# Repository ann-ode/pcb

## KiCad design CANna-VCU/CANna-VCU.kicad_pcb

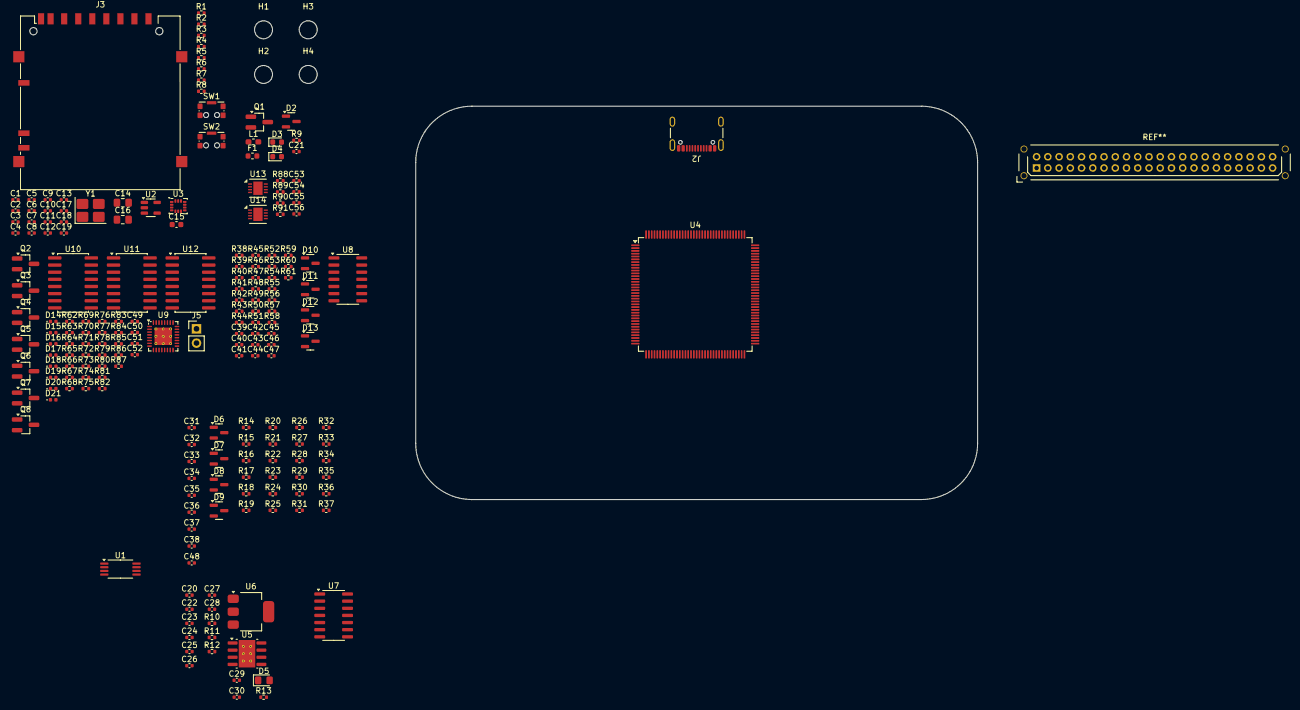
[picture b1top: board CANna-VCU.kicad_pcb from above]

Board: 2 copper layers, 201 parts (0 on the bottom side), 110 nets, no tracks yet.

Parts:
C1, C24, C50, C51: 0.1uF; C_0402_1005Metric
C2, C20, C21: 10uF; C_0402_1005Metric
C3: 68nF; C_0402_1005Metric
C4, C9, C11, C12, C13, C17, C18: 100nF; C_0402_1005Metric
C5, C6, C29, C31, C32, C33, C34, C39, C40, C41, C42, C47, C48, C53, C54: 100n; C_0402_1005Metric
C7, C8: 4.7pF; C_0402_1005Metric
C10: 4.7uF; C_0402_1005Metric
C14, C16: 2.2u; C_0805_2012Metric_Pad1.18x1.45mm_HandSolder
C15: 100nF; C_0603_1608Metric
C19, C23, C49, C52: 1uF; C_0402_1005Metric
C22: 220nF; C_0402_1005Metric
C25, C26, C27, C28: 22uF; C_0402_1005Metric
C30: 10u; C_0402_1005Metric
C35, C36, C37, C38, C43, C44, C45, C46: 1n; C_0402_1005Metric
C55, C56: 4.7n; C_0402_1005Metric
D2: BZX84Cxx; SOT-23
D3, D4: D_Schottky; D_0603_1608Metric
D5: LED; LED_0805_2012Metric_Pad1.15x1.40mm_HandSolder
D6, D7, D8, D9, D10, D11, D12, D13: BZX84-C3V3; SOT-23
D14, D15, D16, D17, D18, D19, D20, D21: LED; LED_0402_1005Metric
F1: 500mA; Fuse_0603_1608Metric
H1, H2, H3, H4: M3; MountingHole_3.2mm_M3
J2: USB_C_Receptacle_USB2.0_16P; USB_C_Receptacle_GCT_USB4105-xx-A_16P_TopMnt_Horizontal
J3: SD_Card_Device; SD_Hirose_DM1AA_SF_PEJ82
J5: FSUK_RTD; PinHeader_1x02_P2.54mm_Vertical
L1: L; L_0603_1608Metric_Pad1.05x0.95mm_HandSolder
Q1, Q2, Q3, Q4, Q5, Q6, Q7, Q8: FDN359BN; SOT-23_Handsoldering
R1, R2: 5.1k; R_0402_1005Metric
R3: 100K; R_0402_1005Metric
R4: 1.3K; R_0402_1005Metric
R5, R6: 10K; R_0402_1005Metric
R7, R8: 2.2K; R_0402_1005Metric
R9, R10, R11, R14, R15, R16, R17, R38, R39, R40, R41: 100k; R_0402_1005Metric
R12: 22k; R_0402_1005Metric
R13: 1k5; R_0402_1005Metric
R18, R19, R20, R21, R42, R43, R44, R45, R76: 1k; R_0402_1005Metric
R22, R26, R30, R34, R46, R50, R54, R58: 75k; R_0402_1005Metric
R23, R24, R27, R28, R31, R32, R35, R36, R47, R48, R51, R52, R55, R56, R59, R60: 5.6k; R_0402_1005Metric
R25, R29, R33, R37, R49, R53, R57, R61: 1.8k; R_0402_1005Metric
R62, R63, R64, R65, R66, R67, R68, R69: 1.5K; R_0402_1005Metric
R70, R71, R72: 8.6K; R_0402_1005Metric
R73, R74, R81, R82, R83, R84: 0; R_0402_1005Metric
R75: 4.7K; R_0402_1005Metric
R77: 3k3; R_0402_1005Metric
R78, R79, R80, R85, R86, R87: 1K; R_0402_1005Metric
R88, R89, R90, R91: 60R; R_0402_1005Metric
SW1, SW2: CK_KMS2xxG; SW_SPST_CK_KMS2xxGP
U1: M24256-DRD; TSSOP-8_4.4x3mm_P0.65mm
U2: MCP9800Ax-xOT; SOT-23-5
U3: ISM330DHCX; LGA-14_3x2.5mm_P0.5mm_LayoutBorder3x4y
U4: STM32F746ZGT6; LQFP-144_20x20mm_P0.5mm
U5: LMR33630CDDA; Texas_R-PDSO-G8_EP2.95x4.9mm_Mask2.4x3.1mm_ThermalVias
U6: LD1117S33TR_SOT223; SOT-223-3_TabPin2
U7, U8: TLV274; SOIC-14_3.9x8.7mm_P1.27mm
U9: TQFN-32-1EP_5x5mm_P0.5mm_EP3.1x3.1mm_ThermalVias
U10, U11, U12: 4504; SOIC-16W_5.3x10.2mm_P1.27mm
U13, U14: LTC2875-DD; DFN-8-1EP_3x3mm_P0.5mm_EP1.66x2.38mm
Y1: 25MHz; Crystal_SMD_3225-4Pin_3.2x2.5mm_HandSoldering

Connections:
0_CANH: R88.2, U13.7 (CANH)
0_CANL: R89.1, U13.6 (CANL)
1_CANH: R90.2, U14.7 (CANH)
1_CANL: R91.1, U14.6 (CANL)
+3V3: C1.2, C2.2, C4.2, C5.2, C6.2, C9.1, C10.1, C11.1, C12.1, C13.1, C15.1, C17.1, C51.2, C52.2, C53.2, C54.2, J3.4 (VDD), R3.2, R5.2, R6.2, R7.2, R8.2, SW1.1, SW2.1, U1.1 (E0), U1.2 (E1), U1.3 (E2), U1.8 (VCC), U2.1 (V_{DD}), U3.5 (VDDIO), U3.8 (VDD), U4.6 (VBAT), U4.17 (VDD), U4.30 (VDD), U4.39 (VDD), U4.52 (VDD), U4.62 (VDD), U4.72 (VDD), U4.84 (VDD), U4.95 (VDDUSB), U4.108 (VDD), U4.121 (VDD), U4.131 (VDD), U4.144 (VDD), U9.28 (RDYEN), U9.31 (VDD3), U10.16 (VDD), U11.1 (VCC), U12.1 (VCC), U13.3 (VCC), U14.3 (VCC)
+3V3A: C18.1, C19.1, U4.33 (VDDA)
+5V: R74.2, R81.2, R82.2
+5V_UNPROT: F1.1, J2.A4 (VBUS), J2.A9 (VBUS), J2.B4 (VBUS), J2.B9 (VBUS)
+12V: C47.2, C48.2, U7.4 (V+), U8.4 (V+)
+GLV_PROT: C20.1, C21.1, C22.1, C49.2, C50.2, D2.3 (K), Q1.2 (S), R70.1, R73.2, R83.2, R84.2, U5.2 (VIN), U5.3 (EN), U9.30 (VDD24)
/ADC/APPS_1_IN: R17.1, R21.1, R41.1, R45.1
/ADC/APPS_1_OUT: C36.2, C44.2, D9.3 (K), D13.3 (K), R35.2, R36.1, R59.2, R60.1
/ADC/APPS_2_IN: R16.1, R20.1, R40.1, R44.1
/ADC/APPS_2_OUT: C35.2, C43.2, D8.3 (K), D12.3 (K), R31.2, R32.1, R55.2, R56.1
/ADC/BPS_IN: R14.1, R18.1, R38.1, R42.1
/ADC/BPS_OUT: C37.2, C45.2, D6.3 (K), D10.3 (K), R23.2, R24.1, R47.2, R48.1
/ADC/SAGL_IN: R15.1, R19.1, R39.1, R43.1
/ADC/SAGL_OUT: C38.2, C46.2, D7.3 (K), D11.3 (K), R27.2, R28.1, R51.2, R52.1
/HSIO/LEVEL1_RDY: R75.2, U9.29 (READY)
/HSIO/LSDI_GP3: U9.15 (OP7), U9.16 (OP8)
/HSIO/LSD_R2D: Q2.1 (G), R77.2
/HSIO/R2DS-: J5.2, R76.2
/MCU/I2C_CLK: U2.4 (SCLK), U3.13 (SCL)
/MCU/I2C_SCL: R8.1, U1.6 (SCL), U4.139 (PB8)
/MCU/I2C_SDA: R7.1, U1.5 (SDA), U2.5 (SDA), U3.14 (SDA), U4.140 (PB9)
/MCU/OSC_IN: C8.1, U4.23 (PH0), Y1.1
/MCU/OSC_OUT: R4.1, U4.24 (PH1)
/MCU/RST: R5.1, U4.25 (NRST)
/MCU/USB_D+: J2.A6 (D+), J2.B6 (D+), U4.104 (PA12)
/MCU/USB_D-: J2.A7 (D-), J2.B7 (D-), U4.103 (PA11)
/MCU/nRST: C3.2, R3.1, U4.134 (PB4)
/Power/+3.3V: C30.1, D5.2 (A), U6.2 (VO)
/Power/BOOT0: C24.1, U5.7 (BOOT)
/Power/FB1: R11.1, R12.2, U5.5 (FB)
/Power/PG1: R10.1, U5.4 (PG)
/Power/PWR_LED_K: D5.1 (K), R13.1
/Power/SW1: C24.2, L1.1, U5.8 (SW)
/Power/VCC1: C23.1, R10.2, U5.6 (VCC)
GND: C1.1, C2.1, C3.1, C4.1, C5.1, C6.1, C7.2, C8.2, C9.2, C10.2, C11.2, C12.2, C13.2, C14.1, C15.2, C16.1, C17.2, C18.2, C19.2, C20.2, C21.2, C22.2, C23.2, C25.2, C26.2, C27.2, C28.2, C29.2, C30.2, C31.1, C32.1, C33.1, C34.1, C35.1, C36.1, C37.1, C38.1, C39.1, C40.1, C41.1, C42.1, C43.1, C44.1, C45.1, C46.1, C47.1, C48.1, C49.1, C50.1, C51.1, C52.1, C53.1, C54.1, C55.2, C56.2, D6.1 (A), D7.1 (A), D8.1 (A), D9.1 (A), D10.1 (A), D11.1 (A), D12.1 (A), D13.1 (A), D14.1 (K), D15.1 (K), D16.1 (K), D17.1 (K), D18.1 (K), D19.1 (K), D20.1 (K), D21.1 (K), J2.A1 (GND), J2.A12 (GND), J2.B1 (GND), J2.B12 (GND), J2.S1 (SHIELD), J3.3 (VSS), J3.6 (VSS), Q2.2 (S), Q3.2 (S), Q4.2 (S), Q5.2 (S), Q6.2 (S), Q7.2 (S), Q8.2 (S), R1.1, R2.1, R9.1, R12.1, R13.2, R14.2, R15.2, R16.2, R17.2, R25.2, R29.2, R33.2, R37.2, R38.2, R39.2, R40.2, R41.2, R49.2, R53.2, R57.2, R61.2, R71.2, R72.2, R75.1, R77.1, SW1.2, SW1.SH (B), SW2.2, SW2.SH (B), U1.4 (VSS), U2.2 (GND), U3.2 (SDx), U3.3 (SCx), U3.6 (GND), U3.7 (GND), U4.16 (VSS), U4.31 (VSSA), U4.38 (VSS), U4.51 (VSS), U4.61 (VSS), U4.83 (VSS), U4.94 (VSS), U4.107 (VSS), U4.120 (VSS), U4.130 (VSS), U5.1 (PGND), U6.1 (GND), U7.11 (V-), U8.11 (V-), U9.25 (GND), U9.32 (GND), U10.8 (VSS), U11.8 (VSS), U12.8 (VSS), U13.2 (GND), U13.8 (RS), U13.9 (GND), U14.2 (GND), U14.8 (RS), U14.9 (GND), Y1.2, Y1.4
unnamed: C7.1, R4.2, Y1.3
unnamed: D2.1 (A), Q1.1 (G), R9.2
unnamed: D3.2 (A), F1.2
unnamed: C29.1, D3.1 (K), D4.1 (K), U6.3 (VI)
unnamed: C25.1, C26.1, C27.1, C28.1, D4.2 (A), L1.2, R11.2
unnamed: D14.2 (A), U9.2 (LED1)
unnamed: D15.2 (A), U9.4 (LED2)
unnamed: D16.2 (A), U9.6 (LED3)
unnamed: D17.2 (A), U9.8 (LED4)
unnamed: D18.2 (A), U9.17 (LED5)
unnamed: D19.2 (A), U9.19 (LED6)
unnamed: D20.2 (A), U9.21 (LED7)
unnamed: D21.2 (A), U9.23 (LED8)
unnamed: J2.A5 (CC1), R1.2
unnamed: J2.B5 (CC2), R2.2
unnamed: J5.1, Q2.3 (D), R76.1
unnamed: Q3.3 (D), R78.1
unnamed: Q4.3 (D), R79.1
unnamed: Q5.3 (D), R80.1
unnamed: Q6.3 (D), R85.1
unnamed: Q7.3 (D), R86.1
unnamed: Q8.3 (D), R87.1
unnamed: R22.2, R23.1
unnamed: R24.2, R25.1
unnamed: R26.2, R27.1
unnamed: R28.2, R29.1
unnamed: R30.2, R31.1
unnamed: R32.2, R33.1
unnamed: R34.2, R35.1
unnamed: R36.2, R37.1
unnamed: R46.2, R47.1
unnamed: R48.2, R49.1
unnamed: R50.2, R51.1
unnamed: R52.2, R53.1
unnamed: R54.2, R55.1
unnamed: R56.2, R57.1
unnamed: R58.2, R59.1
unnamed: R60.2, R61.1
unnamed: C14.2, U4.71 (VCAP_1)
unnamed: C16.2, U4.106 (VCAP_2)
unnamed: C32.2, R19.2, U7.3 (+)
unnamed: R26.1, U7.1, U7.2 (-)
unnamed: C31.2, R18.2, U7.5 (+)
unnamed: R22.1, U7.6 (-), U7.7
unnamed: C34.2, R21.2, U7.10 (+)
unnamed: R34.1, U7.8, U7.9 (-)
unnamed: C33.2, R20.2, U7.12 (+)
unnamed: R30.1, U7.13 (-), U7.14
unnamed: C40.2, R43.2, U8.3 (+)
unnamed: R50.1, U8.1, U8.2 (-)
unnamed: C39.2, R42.2, U8.5 (+)
unnamed: R46.1, U8.6 (-), U8.7
unnamed: C42.2, R45.2, U8.10 (+)
unnamed: R58.1, U8.8, U8.9 (-)
unnamed: C41.2, R44.2, U8.12 (+)
unnamed: R54.1, U8.13 (-), U8.14
unnamed: R70.2, R71.1, U9.27 (EXTVM)
unnamed: R62.1, U9.1 (IN1)
unnamed: R63.1, U9.3 (IN2)
unnamed: R64.1, U9.5 (IN3)
unnamed: R65.1, U9.7 (IN4)
unnamed: R66.1, U9.18 (IN5)
unnamed: R67.1, U9.20 (IN6)
unnamed: R68.1, U9.22 (IN7)
unnamed: R69.1, U9.24 (IN8)
unnamed: R72.1, U9.26 (REFDI)
unnamed: R73.1, R74.1, U10.1 (VCC)
unnamed: R81.1, R83.1, U11.16 (VDD)
unnamed: R82.1, R84.1, U12.16 (VDD)
unnamed: C55.1, R88.1, R89.2, U13.5 (SPLIT)
unnamed: C56.1, R90.1, R91.2, U14.5 (SPLIT)

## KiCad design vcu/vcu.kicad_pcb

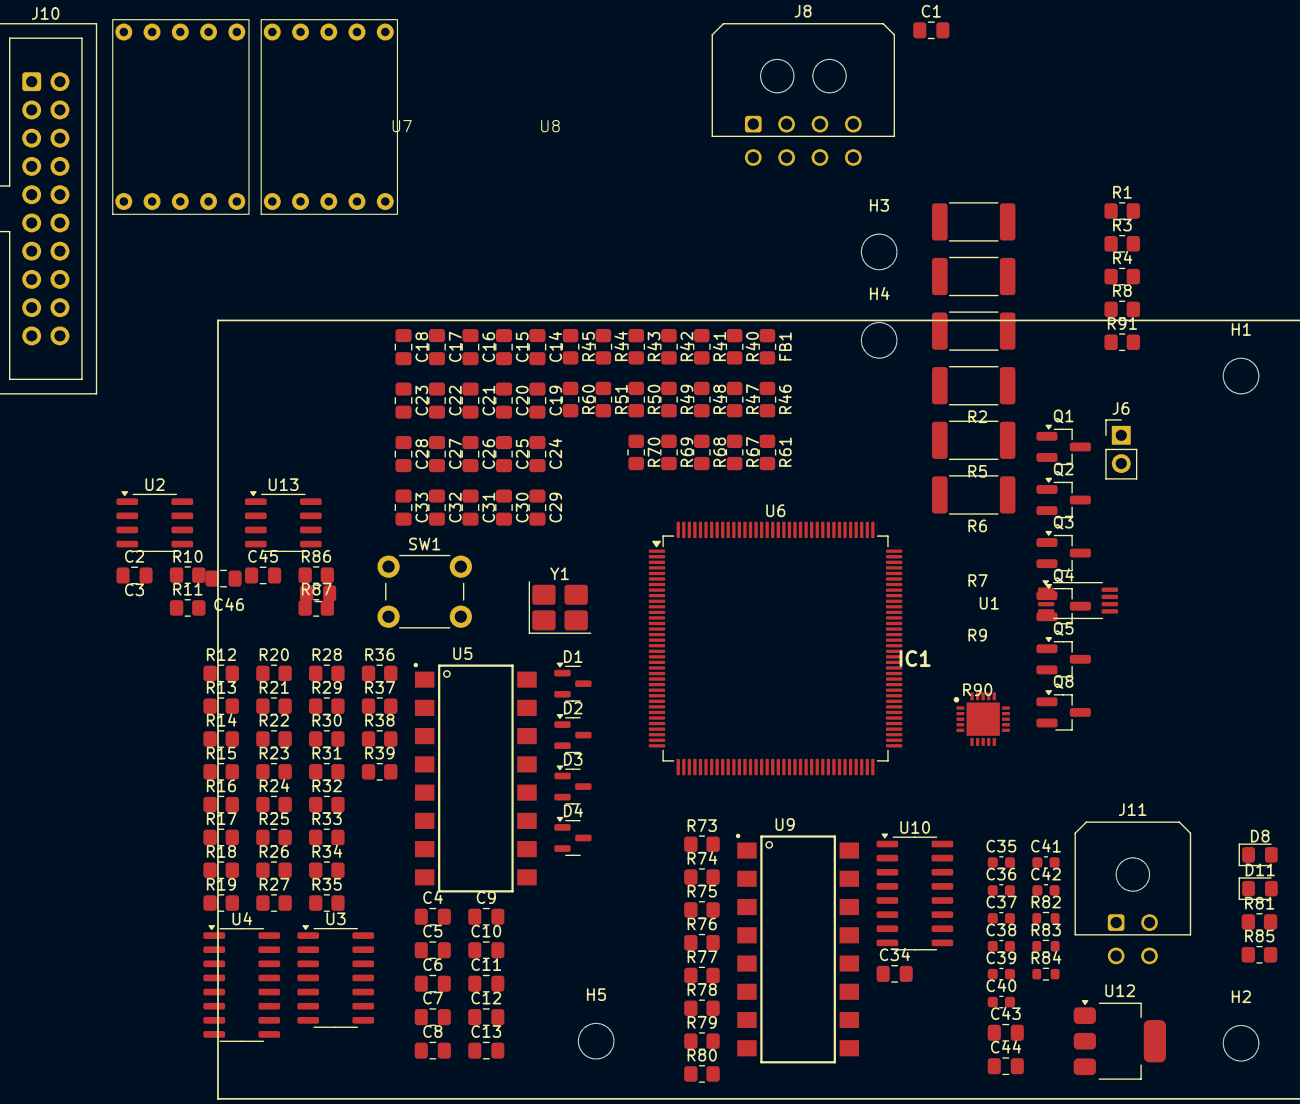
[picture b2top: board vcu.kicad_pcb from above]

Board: 4 copper layers, 157 parts (0 on the bottom side), 123 nets, no tracks yet.

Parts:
C1, C2, C4, C5, C6, C7, C12, C13, C15, C19, C20, C21, C22, C23, C24, C25, C26, C27, C28, C29, C30, C33, C34, C43, C45: 100n; C_0805_2012Metric_Pad1.18x1.45mm_HandSolder
C3, C46: 4.7n; C_0805_2012Metric_Pad1.18x1.45mm_HandSolder
C8, C9, C10, C11: 1n; C_0805_2012Metric_Pad1.18x1.45mm_HandSolder
C14, C16: 4.3p; C_0805_2012Metric_Pad1.18x1.45mm_HandSolder
C17, C18: 2.2u; C_0805_2012Metric_Pad1.18x1.45mm_HandSolder
C31: 4.7u; C_0805_2012Metric_Pad1.18x1.45mm_HandSolder
C32: 1u; C_0805_2012Metric_Pad1.18x1.45mm_HandSolder
C35: 10uF; C_0603_1608Metric
C36: 220nF; C_0603_1608Metric
C37: 1uF; C_0603_1608Metric
C38: 0.1uF; C_0603_1608Metric
C39, C40, C41, C42: 22uF; C_0603_1608Metric
C44: 10u; C_0805_2012Metric_Pad1.18x1.45mm_HandSolder
D1, D2, D3, D4: BZX84-C3V3; SOT-23
D8, D11: LED; LED_0805_2012Metric_Pad1.15x1.40mm_HandSolder
FB1: 120; R_0805_2012Metric_Pad1.20x1.40mm_HandSolder
H1, H2, H3, H4, H5: M3; MountingHole_3.2mm_M3
IC1: MAX20040DATPA_VY+; QFN50P400X400X80-21N-D
J6: FSUK_RTD; PinHeader_1x02_P2.54mm_Vertical
J8: OUT; Molex_Micro-Fit_3.0_43045-0800_2x04_P3.00mm_Horizontal
J10: Conn_ARM_JTAG_SWD_20; IDC-Header_2x10_P2.54mm_Vertical
J11: PWR; Molex_Micro-Fit_3.0_43045-0400_2x02_P3.00mm_Horizontal
Q1, Q2, Q3, Q4, Q5, Q8: FDN359BN; SOT-23_Handsoldering
R1, R3, R4, R40, R60, R61, R67, R68, R69, R70, R77, R78, R79, R80, R91: 10k; R_0805_2012Metric_Pad1.20x1.40mm_HandSolder
R2, R5, R6, R7, R9, R90: 1k; R_2512_6332Metric_Pad1.40x3.35mm_HandSolder
R8: 3k3; R_0805_2012Metric_Pad1.20x1.40mm_HandSolder
R10, R11, R86, R87: 60R; R_0805_2012Metric_Pad1.20x1.40mm_HandSolder
R12, R13, R14, R15: 100k; R_0805_2012Metric_Pad1.20x1.40mm_HandSolder
R16, R17, R18, R19, R36, R37, R38, R39: 1k; R_0805_2012Metric_Pad1.20x1.40mm_HandSolder
R20, R24, R28, R32: 75k; R_0805_2012Metric_Pad1.20x1.40mm_HandSolder
R21, R22, R25, R26, R29, R30, R33, R34: 5.6k; R_0805_2012Metric_Pad1.20x1.40mm_HandSolder
R23, R27, R31, R35: 1.8k; R_0805_2012Metric_Pad1.20x1.40mm_HandSolder
R41, R42, R43, R44, R45, R46, R47, R48, R49, R50, R51: 100; R_0805_2012Metric_Pad1.20x1.40mm_HandSolder
R73, R74, R75, R76: 220; R_0805_2012Metric_Pad1.20x1.40mm_HandSolder
R81: 3.3k; R_0805_2012Metric_Pad1.20x1.40mm_HandSolder
R82, R83: 100k; R_0603_1608Metric
R84: 22k; R_0603_1608Metric
R85: 1k5; R_0805_2012Metric_Pad1.20x1.40mm_HandSolder
SW1: SW_Push; SW_PUSH_6mm
U1: M24256-DRD; TSSOP-8_4.4x3mm_P0.65mm
U2, U13: MAX3051ESA+; SOIC-8_3.9x4.9mm_P1.27mm
U3: TLV274; SOIC-14_3.9x8.7mm_P1.27mm
U4, U10: HCF4010; SOIC-16_3.9x9.9mm_P1.27mm
U5, U9: ILQ615-4X009T; SOIC254P1005X380-16N
U6: STM32F746ZGT6; LQFP-144_20x20mm_P0.5mm
U7, U8: Vishay TDSG5160-MN 7-Segment Display
U12: LD1117S33TR_SOT223; SOT-223-3_TabPin2
Y1: 8MHz; Crystal_SMD_3225-4Pin_3.2x2.5mm_HandSoldering

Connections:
+3.3V: C1.1, C2.2, C19.1, C20.1, C21.1, C22.1, C23.1, C24.1, C25.1, C26.1, C27.1, C28.1, C29.1, C30.1, C31.1, C32.1, C44.1, C45.2, D11.2 (A), FB1.2, J10.1 (VTREF), J10.2 (VCC/NC), R60.2, R61.1, R67.2, R69.2, R70.2, U1.1 (E0), U1.2 (E1), U1.3 (E2), U1.8 (VCC), U2.3 (VDD), U5.10, U5.12, U5.14, U5.16, U6.6 (VBAT), U6.17 (VDD), U6.30 (VDD), U6.39 (VDD), U6.52 (VDD), U6.62 (VDD), U6.72 (VDD), U6.84 (VDD), U6.95 (VDDUSB), U6.108 (VDD), U6.121 (VDD), U6.131 (VDD), U6.144 (VDD), U12.2 (VO), U13.3 (VDD)
+3.3VA: C33.1, FB1.1, U6.32 (VREF+), U6.33 (VDDA)
+12V: C12.2, C13.2, C34.2, C35.1, C36.1, D8.2 (A), IC1.13 (IN), J8.5, U3.4 (V+), U4.1 (VCC), U4.16 (VDD), U9.10, U9.12, U9.14, U9.16, U10.1 (VCC), U10.16 (VDD)
+12VA: IC1.15 (OUT), IC1.16 (OUT_S)
/APPS_1_IN: R15.1, R19.1
/APPS_2_IN: R14.1, R18.1
/BMS_LATCHING_IN: Q2.3 (D), R5.2
/BPS_IN: R12.1, R16.1
/BRAKE_PRESSED: J8.2, U10.4 (Bout)
/CAN_C_H: R86.2, U13.7 (CANH)
/CAN_C_L: R87.1, U13.6 (CANL)
/CAN_S_H: R10.2, U2.7 (CANH)
/CAN_S_L: R11.1, U2.6 (CANL)
/DRS_BTN: R91.1, U4.9 (Din)
/DRS_PWM: J8.6, U10.10 (Dout)
/EEPROM_SCL: R61.2, U1.6 (SCL), U6.139 (PB8)
/EEPROM_SDA: R60.1, U1.5 (SDA), U6.140 (PB9)
/EEPROM_WC: U1.7 (WC), U6.96 (PC6)
/IMD_LATCHING_IN: Q1.3 (D), R2.2
/Input Shift/APPS_1_OUT: C9.2, D4.3 (K), R33.2, R34.1, U6.37 (PA3)
/Input Shift/APPS_2_OUT: C8.2, D3.3 (K), R29.2, R30.1, U6.29 (PC3)
/Input Shift/BPS_OUT: C10.2, D1.3 (K), R21.2, R22.1, U6.26 (PC0)
/Input Shift/DOUT_1: U5.15, U6.11 (PF1)
/Input Shift/DOUT_2: U5.13, U6.12 (PF2)
/Input Shift/DOUT_3: U5.11, U6.15 (PF5)
/Input Shift/DOUT_4: U5.9, U6.22 (PF10)
/Input Shift/SAGL_OUT: C11.2, D2.3 (K), R25.2, R26.1, U6.13 (PF3)
/Output Level Shifting/DIN_1: R73.1, U6.60 (PE9)
/Output Level Shifting/DIN_2: R74.1, U6.64 (PE11)
/Output Level Shifting/DIN_3: R75.1, U6.54 (PF14)
/Output Level Shifting/DIN_4: R76.1, U6.34 (PA0)
/Power/FB1: R83.1, R84.2
/Power/PWR_LED_K: D11.1 (K), R85.1
/Power/VCC1: C37.1, R82.2
/R2D_BTN: R3.1, U4.5 (Bin)
/R2D_SIREN_ON: Q5.1 (G), R8.2, U6.55 (PF15)
/RTDS-: J6.2, R9.2
/SAGL_IN: R13.1, R17.1
/SHDN_STATE: R1.1, U4.3 (Ain)
/STATUS: J8.1, U10.2 (Aout)
/STM32-F746ZG/7_SEG_A: U7.7 (A), U8.7 (A)
/STM32-F746ZG/7_SEG_B: U7.6 (B), U8.6 (B)
/STM32-F746ZG/7_SEG_C: U7.4 (C), U8.4 (C)
/STM32-F746ZG/7_SEG_D: U7.2 (D), U8.2 (D)
/STM32-F746ZG/7_SEG_DP: U7.5 (DP), U8.5 (DP)
/STM32-F746ZG/7_SEG_E: U7.1 (E), U8.1 (E)
/STM32-F746ZG/7_SEG_F: U7.9 (F), U8.9 (F)
/STM32-F746ZG/7_SEG_G: U7.10 (G), U8.10 (G)
/STM32-F746ZG/BOOT0: R40.2, U6.138 (BOOT0)
/STM32-F746ZG/CAN1_RX: U6.114 (PD0), U13.4 (RXD)
/STM32-F746ZG/CAN1_TX: U6.115 (PD1), U13.1 (TXD)
/STM32-F746ZG/CAN2_RX: U2.4 (RXD), U6.73 (PB12)
/STM32-F746ZG/CAN2_TX: U2.1 (TXD), U6.136 (PB6)
/STM32-F746ZG/TCK/SWDCLK: J10.9 (TCK/SWCLK), R68.2, U6.109 (PA14)
/STM32-F746ZG/TDI: J10.5 (TDI), R69.1, U6.110 (PA15)
/STM32-F746ZG/TDO/SWO: J10.13 (TDO/SWO), U6.133 (PB3)
/STM32-F746ZG/TMS/SWDIO: J10.7 (TMS/SWDIO), R67.1, U6.105 (PA13)
/STM32-F746ZG/TRST: J10.3 (~TRST), R70.1, U6.134 (PB4)
/TS_ON: J8.3, U10.6 (Cout)
/TS_ON_BTN: R4.1, U4.7 (Cin)
/VC_LEDS_ON: Q1.1 (G), Q2.1 (G), Q3.1 (G), Q4.1 (G), Q8.1 (G), U6.2 (PE3), U6.3 (PE4), U6.4 (PE5), U6.5 (PE6)
GND: C1.2, C2.1, C3.2, C4.1, C5.1, C6.1, C7.1, C8.1, C9.1, C10.1, C11.1, C12.1, C13.1, C14.2, C15.2, C16.2, C17.1, C18.1, C19.2, C20.2, C21.2, C22.2, C23.2, C24.2, C25.2, C26.2, C27.2, C28.2, C29.2, C30.2, C31.2, C32.2, C33.2, C34.1, C35.2, C36.2, C37.2, C39.2, C40.2, C41.2, C42.2, C43.2, C44.2, C45.1, C46.2, D1.1 (A), D2.1 (A), D3.1 (A), D4.1 (A), IC1.1 (PGND2), IC1.5 (AGND1), IC1.12 (AGND2), IC1.14 (PGND1), IC1.TP, J8.4, J8.7, J8.8, J10.4 (GND), J10.6 (GND), J10.8 (GND), J10.10 (GND), J10.11 (RTCK), J10.12 (GND), J10.14 (GND), J10.16 (GND), J10.18 (GND), J10.20 (GND), J11.2, J11.4, Q1.2 (S), Q2.2 (S), Q3.2 (S), Q4.2 (S), Q5.2 (S), Q8.2 (S), R1.2, R3.2, R4.2, R8.1, R12.2, R13.2, R14.2, R15.2, R23.2, R27.2, R31.2, R35.2, R68.1, R77.2, R78.2, R79.2, R80.2, R81.2, R84.1, R85.2, R91.2, SW1.1, U1.4 (VSS), U2.2 (GND), U2.8 (RS), U3.11 (V-), U4.8 (VSS), U4.11 (Ein), U4.14 (Fin), U5.2, U5.4, U5.6, U5.8, U6.16 (VSS), U6.31 (VSSA), U6.38 (VSS), U6.51 (VSS), U6.61 (VSS), U6.83 (VSS), U6.94 (VSS), U6.107 (VSS), U6.120 (VSS), U6.130 (VSS), U9.2, U9.4, U9.6, U9.8, U10.8 (VSS), U10.11 (Ein), U10.14 (Fin), U12.1 (GND), U13.2 (GND), U13.8 (RS), Y1.2, Y1.4
NRST+: C15.1, SW1.2, U6.25 (NRST)
unnamed: C3.1, R10.1, R11.2
unnamed: C46.1, R86.1, R87.2
unnamed: D8.1 (K), R81.1
unnamed: C39.1, C40.1, C41.1, C42.1, R83.2
unnamed: C43.1, U12.3 (VI)
unnamed: IC1.4 (VCC), IC1.10 (FB)
unnamed: J6.1, Q5.3 (D), R9.1
unnamed: J11.1, J11.3
unnamed: Q3.3 (D), R6.2
unnamed: Q4.3 (D), R7.2
unnamed: U7.3 (CC), U7.8 (CC)
unnamed: U8.3 (CC), U8.8 (CC)
unnamed: Q8.3 (D), R90.2
unnamed: R20.2, R21.1
unnamed: R22.2, R23.1
unnamed: R24.2, R25.1
unnamed: R26.2, R27.1
unnamed: R28.2, R29.1
unnamed: R30.2, R31.1
unnamed: R32.2, R33.1
unnamed: R34.2, R35.1
unnamed: R36.2, U5.1
unnamed: R37.2, U5.3
unnamed: R38.2, U5.5
unnamed: R39.2, U5.7
unnamed: R73.2, U9.1
unnamed: R74.2, U9.3
unnamed: R75.2, U9.5
unnamed: R76.2, U9.7
unnamed: C5.2, R17.2, U3.3 (+)
unnamed: R24.1, U3.1, U3.2 (-)
unnamed: C4.2, R16.2, U3.5 (+)
unnamed: R20.1, U3.6 (-), U3.7
unnamed: C7.2, R19.2, U3.10 (+)
unnamed: R32.1, U3.8, U3.9 (-)
unnamed: C6.2, R18.2, U3.12 (+)
unnamed: R28.1, U3.13 (-), U3.14
unnamed: R36.1, U4.2 (Aout)
unnamed: R37.1, U4.4 (Bout)
unnamed: R38.1, U4.6 (Cout)
unnamed: R39.1, U4.10 (Dout)
unnamed: R41.2, U6.57 (PG1)
unnamed: R42.2, U6.87 (PG2)
unnamed: R43.2, U6.88 (PG3)
unnamed: R44.2, U6.89 (PG4)
unnamed: R45.2, U6.90 (PG5)
unnamed: R46.2, U6.91 (PG6)
unnamed: R47.2, U6.92 (PG7)
unnamed: R48.2, U6.93 (PG8)
unnamed: R49.2, U6.124 (PG9)
unnamed: R50.2, U6.125 (PG10)
unnamed: R51.2, U6.126 (PG11)
unnamed: C14.1, U6.23 (PH0), Y1.1
unnamed: C16.1, U6.24 (PH1), Y1.3
unnamed: C17.2, U6.71 (VCAP_1)
unnamed: C18.2, U6.106 (VCAP_2)
unnamed: R80.1, U9.15, U10.3 (Ain)
unnamed: R79.1, U9.13, U10.5 (Bin)
unnamed: R78.1, U9.11, U10.7 (Cin)
unnamed: R77.1, U9.9, U10.9 (Din)

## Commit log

2025-11-11 added planned change notes
    mwuhahahahahhah im tearing this thing to pieces
2025-11-13 added new vcu project
2025-11-15 first draft of full board
2025-11-16 tidying up
2025-11-20 added power managment bits
